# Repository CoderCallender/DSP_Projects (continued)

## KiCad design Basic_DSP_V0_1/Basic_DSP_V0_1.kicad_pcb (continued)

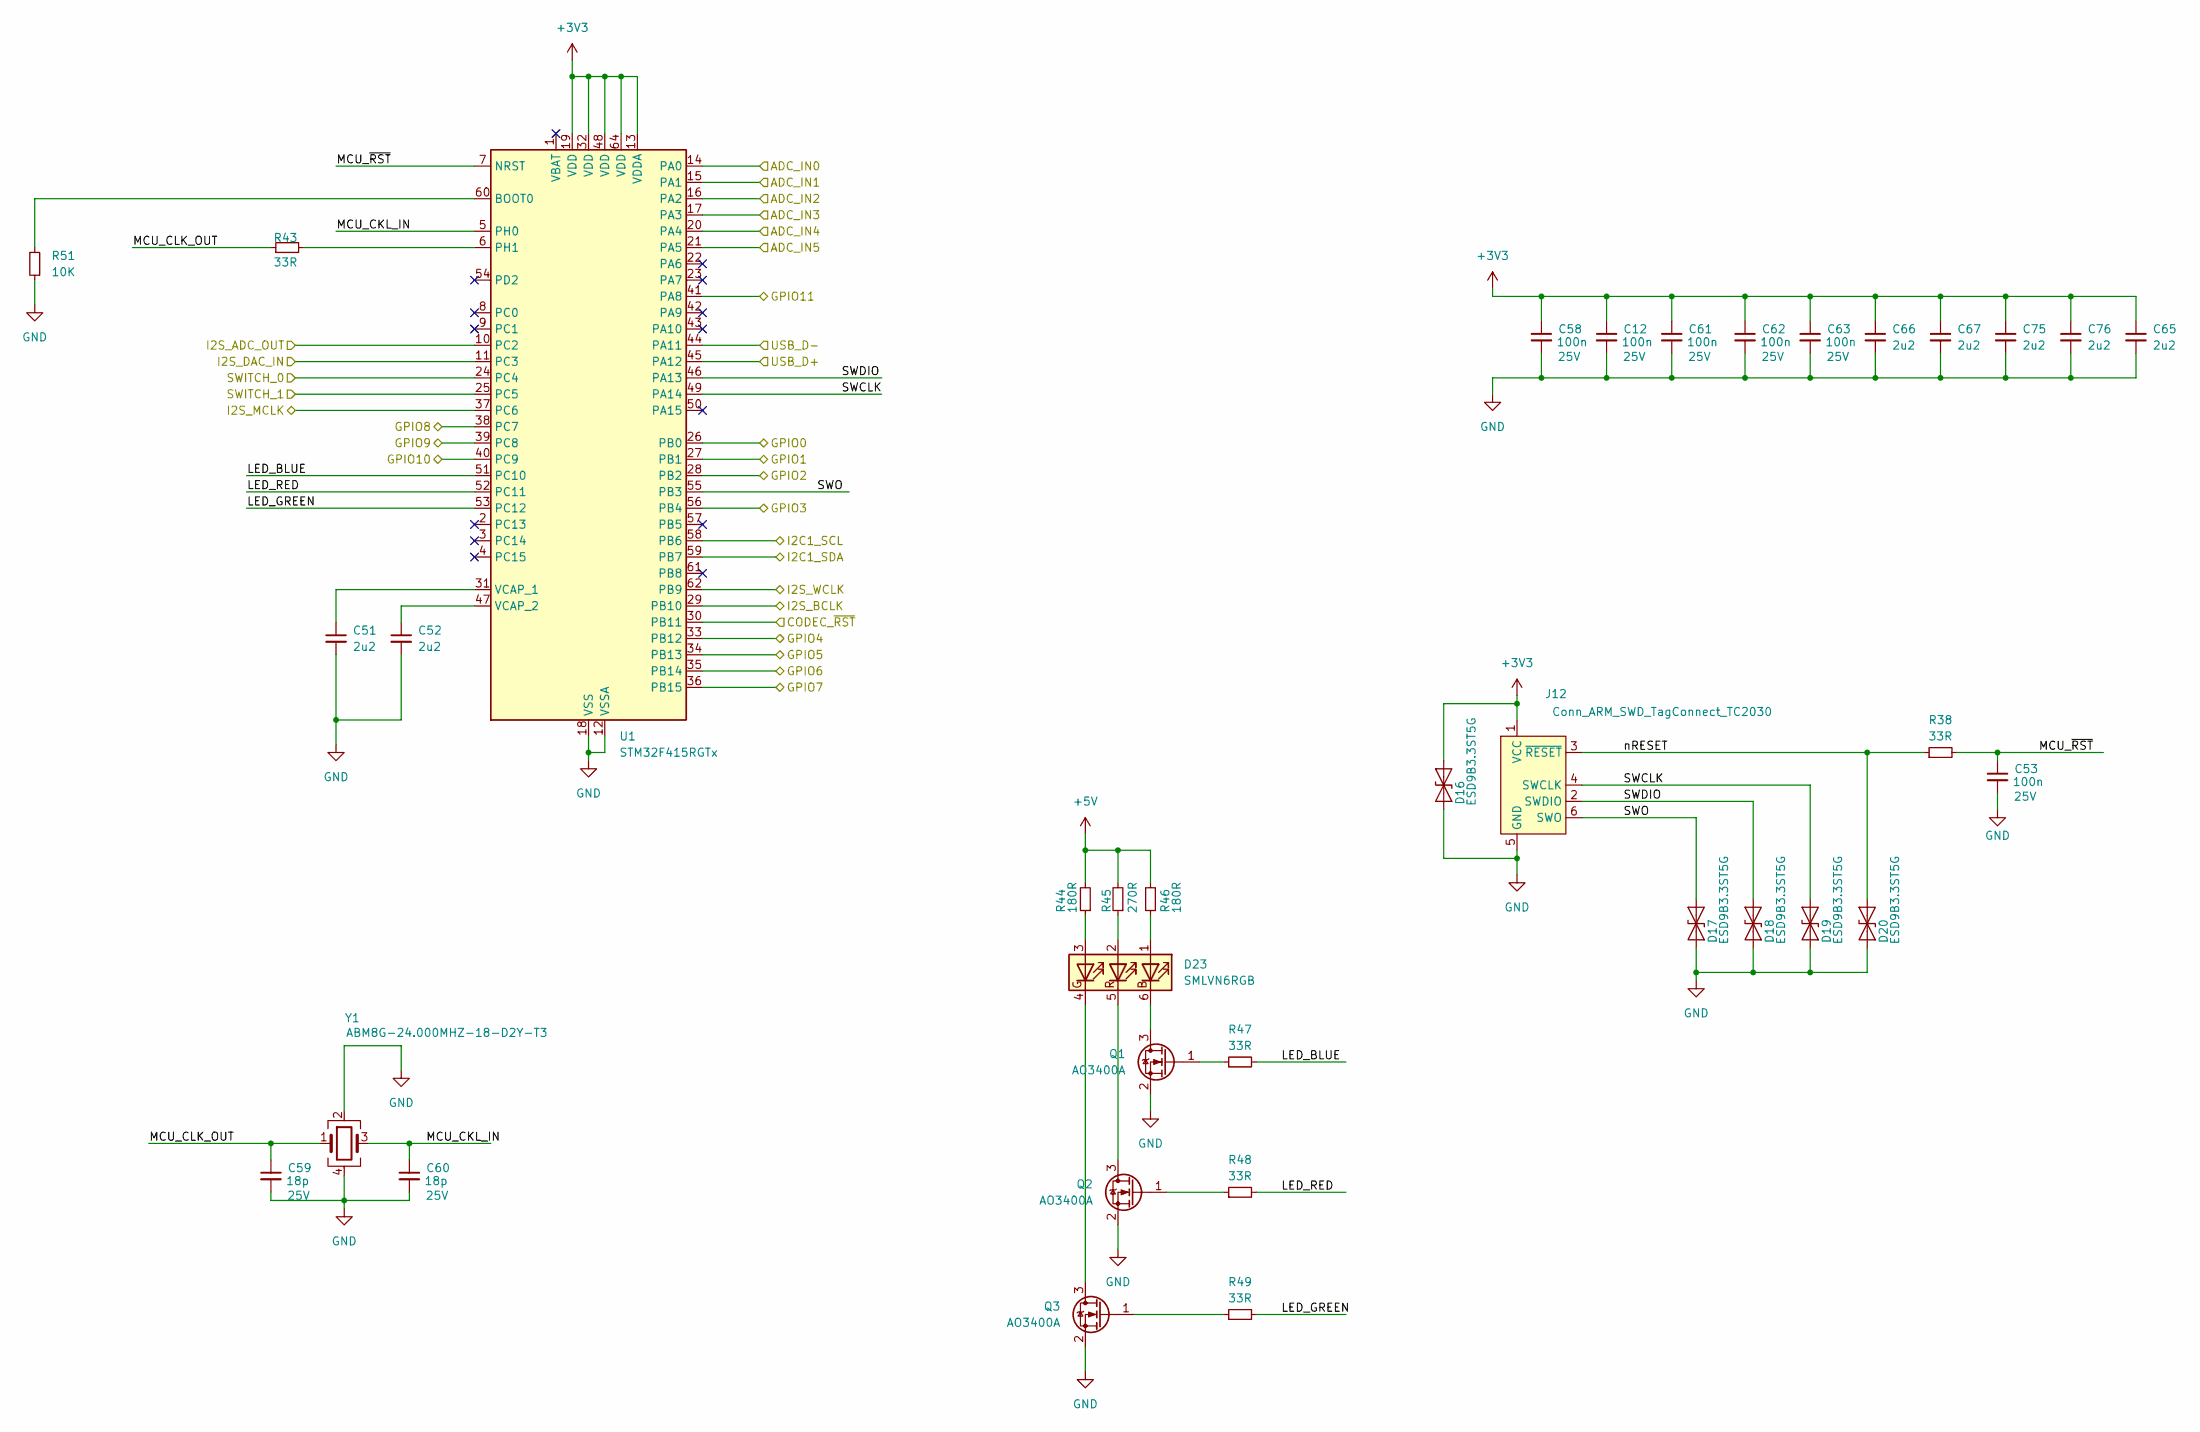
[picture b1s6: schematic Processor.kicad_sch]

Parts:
C12, C53, C58, C61, C62, C63: 100n; C_0603_1608Metric_Pad1.08x0.95mm_HandSolder; Voltage 25V; MPN 0603B104M250NT
C51, C52, C65, C66, C67, C75, C76: 2u2; C_0603_1608Metric_Pad1.08x0.95mm_HandSolder; Voltage 25V; MPN 0603B225K250NT
C59, C60: 18p; C_0603_1608Metric_Pad1.08x0.95mm_HandSolder; Voltage 25V; MPN RF18N180F500CT
D16, D17, D18, D19, D20: ESD9B3.3ST5G; D_SOD-923; MPN ESD9B3.3ST5G
D23: SMLVN6RGB; LED_ROHM_SMLVN6; MPN SMLVN6RGB1W1
J12: Conn_ARM_SWD_TagConnect_TC2030; Tag-Connect_TC2030-IDC-FP_2x03_P1.27mm_Vertical
Q1, Q2, Q3: AO3400A; SOT-23; MPN AO3400A
R38, R43, R47, R48, R49: 33R; R_0603_1608Metric_Pad0.98x0.95mm_HandSolder; MPN WR06X33R0FTL
R44, R46: 180R; R_0603_1608Metric_Pad0.98x0.95mm_HandSolder; MPN 0603WAF1800T5E
R45: 270R; R_0603_1608Metric_Pad0.98x0.95mm_HandSolder; MPN 0603WAF2700T5E
R51: 10K; R_0603_1608Metric_Pad0.98x0.95mm_HandSolder; MPN 0603WAF1002T5E
U1: STM32F415RGTx; LQFP-64_10x10mm_P0.5mm; MPN STM32F415RGT6
Y1: ABM8G-24.000MHZ-18-D2Y-T3; Crystal_SMD_Abracon_ABM8G-4Pin_3.2x2.5mm

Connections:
+3V3: C12.1, C58.1, C61.1, C62.1, C63.1, C65.1, C66.1, C67.1, C75.1, C76.1, D16.2 (A2), J12.1 (VCC), U1.13 (VDDA), U1.19 (VDD), U1.32 (VDD), U1.48 (VDD), U1.64 (VDD); also elsewhere on the board
+5V: R44.2, R45.2, R46.2; also elsewhere on the board
/CODEC/CODEC_~RST: U1.30 (PB11); also elsewhere on the board
/CODEC/I2C1_SCL: U1.58 (PB6); also elsewhere on the board
/CODEC/I2C1_SDA: U1.59 (PB7); also elsewhere on the board
/CODEC/I2S_ADC_OUT: U1.10 (PC2); also elsewhere on the board
/CODEC/I2S_BCLK: U1.29 (PB10); also elsewhere on the board
/CODEC/I2S_DAC_IN: U1.11 (PC3); also elsewhere on the board
/CODEC/I2S_MCLK: U1.37 (PC6); also elsewhere on the board
/CODEC/I2S_WCLK: U1.62 (PB9); also elsewhere on the board
/Connections/ADC_IN0: U1.14 (PA0); also elsewhere on the board
/Connections/ADC_IN1: U1.15 (PA1); also elsewhere on the board
/Connections/ADC_IN2: U1.16 (PA2); also elsewhere on the board
/Connections/ADC_IN3: U1.17 (PA3); also elsewhere on the board
/Connections/ADC_IN4: U1.20 (PA4); also elsewhere on the board
/Connections/ADC_IN5: U1.21 (PA5); also elsewhere on the board
/Connections/GPIO0: U1.26 (PB0); also elsewhere on the board
/Connections/GPIO1: U1.27 (PB1); also elsewhere on the board
/Connections/GPIO2: U1.28 (PB2); also elsewhere on the board
/Connections/GPIO3: U1.56 (PB4); also elsewhere on the board
/Connections/GPIO4: U1.33 (PB12); also elsewhere on the board
/Connections/GPIO5: U1.34 (PB13); also elsewhere on the board
/Connections/GPIO6: U1.35 (PB14); also elsewhere on the board
/Connections/GPIO7: U1.36 (PB15); also elsewhere on the board
/Connections/GPIO8: U1.38 (PC7); also elsewhere on the board
/Connections/GPIO9: U1.39 (PC8); also elsewhere on the board
/Connections/GPIO10: U1.40 (PC9); also elsewhere on the board
/Connections/GPIO11: U1.41 (PA8); also elsewhere on the board
/Connections/SWITCH_0: U1.24 (PC4); also elsewhere on the board
/Connections/SWITCH_1: U1.25 (PC5); also elsewhere on the board
/Connections/USB_D+: U1.45 (PA12); also elsewhere on the board
/Connections/USB_D-: U1.44 (PA11); also elsewhere on the board
/Processor/LED_BLUE: R47.2, U1.51 (PC10)
/Processor/LED_GREEN: R49.2, U1.53 (PC12)
/Processor/LED_RED: R48.2, U1.52 (PC11)
/Processor/MCU_CKL_IN: C60.1, U1.5 (PH0), Y1.3
/Processor/MCU_CLK_OUT: C59.1, R43.1, Y1.1
/Processor/MCU_~RST: C53.1, R38.2, U1.7 (NRST)
/Processor/SWCLK: D19.2 (A2), J12.4 (SWCLK), U1.49 (PA14)
/Processor/SWDIO: D18.2 (A2), J12.2 (SWDIO), U1.46 (PA13)
/Processor/SWO: D17.2 (A2), J12.6 (SWO), U1.55 (PB3)
/Processor/nRESET: D20.2 (A2), J12.3 (~RESET), R38.1
GND: C12.2, C51.2, C52.2, C53.2, C58.2, C59.2, C60.2, C61.2, C62.2, C63.2, C65.2, C66.2, C67.2, C75.2, C76.2, D16.1 (A1), D17.1 (A1), D18.1 (A1), D19.1 (A1), D20.1 (A1), J12.5 (GND), Q1.2 (S), Q2.2 (S), Q3.2 (S), R51.1, U1.12 (VSSA), U1.18 (VSS), U1.63 (VSS), Y1.2, Y1.4; also elsewhere on the board
unnamed: D23.1 (BA), R46.1
unnamed: D23.6 (BK), Q1.3 (D)
unnamed: D23.3 (GA), R44.1
unnamed: D23.4 (GK), Q3.3 (D)
unnamed: D23.2 (RA), R45.1
unnamed: D23.5 (RK), Q2.3 (D)
unnamed: Q1.1 (G), R47.1
unnamed: Q2.1 (G), R48.1
unnamed: Q3.1 (G), R49.1
unnamed: R51.2, U1.60 (BOOT0)
unnamed: R43.2, U1.6 (PH1)
unnamed: C51.1, U1.31 (VCAP_1)
unnamed: C52.1, U1.47 (VCAP_2)

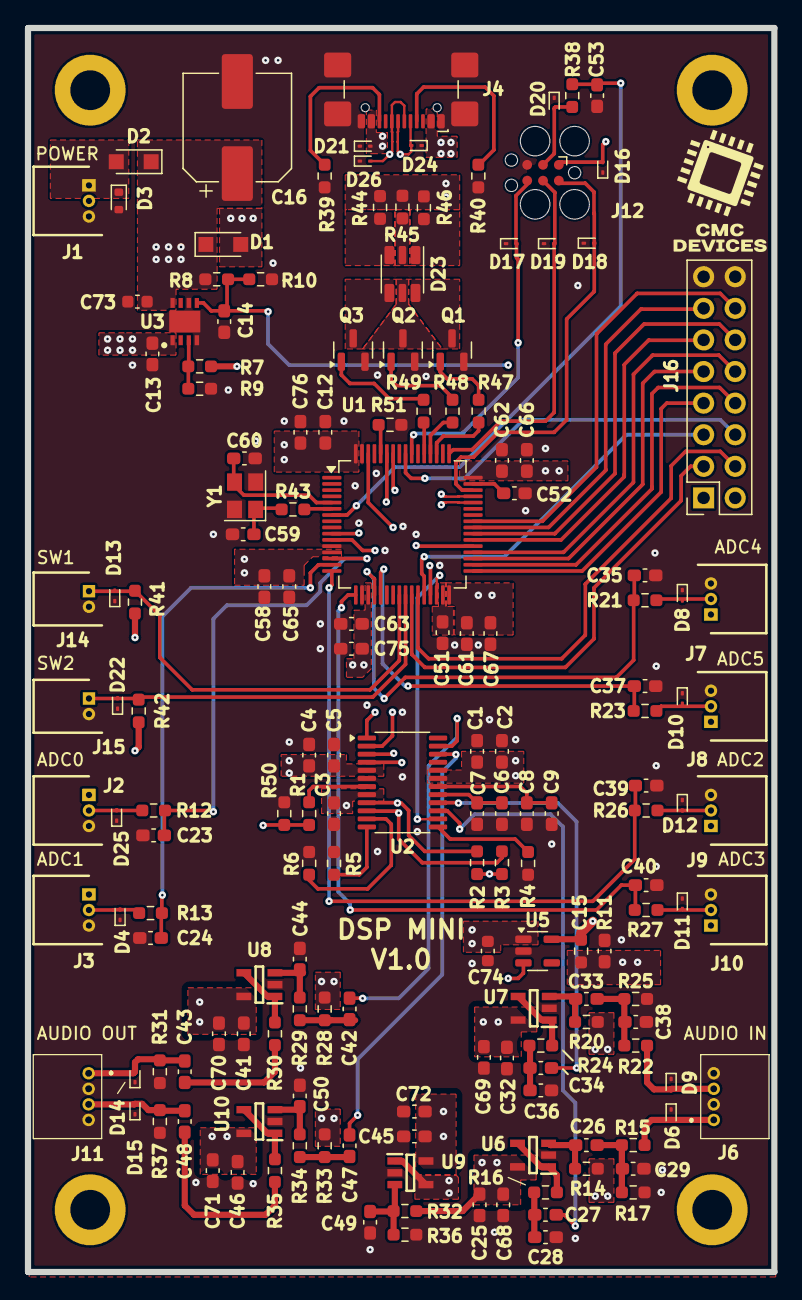
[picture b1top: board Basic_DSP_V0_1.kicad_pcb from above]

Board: 6 copper layers, 60.0 x 100.0 mm, 165 parts (0 on the bottom side), 102 nets.

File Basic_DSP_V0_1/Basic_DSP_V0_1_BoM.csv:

Comment,Designator,Footprint,JLCPCB Part #,Qty,DNP,MF,MPN,Manufacturer_Part_Number,Mouser Part Number,OC_MOUSER,Voltage
220uF,C16,Capacitor_SMD:CP_Elec_8x10.5,C5162357,1,,ROQANG ,CK1V221M-CRF10,,,,35V
100n,"C1,C3,C5,C6,C8,C12,C14,C23,C24,C25,C32,C35,C37,C39,C40,C41,C45,C46,C53,C58,C61,C62,C63",Capacitor_SMD:C_0603_1608Metric_Pad1.08x0.95mm_HandSolder,C336628,23,,FH (Guangdong Fenghua Advanced Tech) ,0603B104M250NT,,,963-BAST105SB7104KF,25V
22u,"C15,C49",Capacitor_SMD:C_0603_1608Metric_Pad1.08x0.95mm_HandSolder,C6119868,2,,HRE,CGA0603X5R226M160JT,,,187-CL32B226MOJNNNE,16V
2u2,"C2,C4,C13,C51,C52,C65,C66,C67,C68,C69,C70,C71,C72,C75,C76",Capacitor_SMD:C_0603_1608Metric_Pad1.08x0.95mm_HandSolder,C99228,15,,FH (Guangdong Fenghua Advanced Tech) ,0603B225K250NT,,,-- mixed values --,25V
10n,"C26,C33,C42,C47",Capacitor_SMD:C_0603_1608Metric_Pad1.08x0.95mm_HandSolder,C445734,4,,TDK ,CGA3E2X8R2A103KT0Y0H,,,,
220p,"C28,C29,C36,C38",Capacitor_SMD:C_0603_1608Metric_Pad1.08x0.95mm_HandSolder,C302062,4,,Walsin Tech Corp,0603N221J500CT,,,,
1n,"C44,C50",Capacitor_SMD:C_0603_1608Metric_Pad1.08x0.95mm_HandSolder,C161114,2,,Murata Electronics ,GCJ188R71H102KA01D,,,,
18p,"C59,C60",Capacitor_SMD:C_0603_1608Metric_Pad1.08x0.95mm_HandSolder,C2909435,2,,Walsin Tech Corp ,RF18N180F500CT,,,963-BAST105SB7104KF,25V
10u,"C7,C9,C27,C34,C43,C48",Capacitor_SMD:C_0603_1608Metric_Pad1.08x0.95mm_HandSolder,C96446,6,,Samsung Electro-Mechanics ,CL10A106MA8NRNC,,,-- mixed values --,-- mixed values --
10uF,"C73,C74",Capacitor_SMD:C_0603_1608Metric,C96446,2,,Samsung Electro-Mechanics ,CL10A106MA8NRNC,,,581-06033D106MAT2A,
ESD5Z12T1G/T5G,D3,Diode_SMD:D_SOD-523,C7436544,1,,FUXINSEMI,ESD5Z12T1G,,,,12V
SMLVN6RGB,D23,LED_SMD:LED_ROHM_SMLVN6,C2842809,1,,ROHM Semicon,SMLVN6RGB1W1,,,,
PMEG4030ER,"D1,D2",Diode_SMD:Nexperia_CFP3_SOD-123W,C5366303,2,,Shikues ,PMEG4030ER,,,,
ESD9B3.3ST5G,"D4,D8,D10,D11,D12,D13,D16,D17,D18,D19,D20,D22,D25",Diode_SMD:D_SOD-923,C3040608,13,,TECH PUBLIC ,ESD9B3.3ST5G,,,,
ESD9B5.0ST5G,"D6,D9,D14,D15,D21,D24,D26",Diode_SMD:D_SOD-923,C3021104,7,,TECH PUBLIC , ESD9B5.0ST5G,,,,
USB_C_Receptacle_USB2.0_16P,J4,Connector_USB:USB_C_Receptacle_GCT_USB4110,,1,,,,,,,
Conn_02x08_Odd_Even,J16,Connector_PinSocket_2.54mm:PinSocket_2x08_P2.54mm_Vertical,,1,,DNP,,,,,
53048-0310,"J1,J2,J3,J7,J8,J9,J10",Chase_Conn:SHDRRA3W35P0X125_1X3_550X550X350P,C505275,7,, MOLEX ,530480310,53048-0310,538-53048-0310,,
53048-0210,"J14,J15",Chase_Conn:SHDRRA2W35P0X125_1X2_425X550X350P,C505099,2,,MOLEX,530480210,53048-0210,538-53048-0210,,
53048-0410,"J6,J11",Chase_Conn:530480410,C588275,2,,MOLEX,530480410,53048-0410,538-53048-0410,,
AO3400A,"Q1,Q2,Q3",Package_TO_SOT_SMD:SOT-23,C20917,3,,Alpha & Omega Semicon ,AO3400A,,,,
0R,R7,Resistor_SMD:R_0603_1608Metric_Pad0.98x0.95mm_HandSolder,C21189,1,,UNI-ROYAL(Uniroyal Elec) ,0603WAF0000T5E,,,,
0R,R11,Resistor_SMD:R_0603_1608Metric_Pad0.98x0.95mm_HandSolder,C22859,1,,UNI-ROYAL(Uniroyal Elec) ,0603WAF100JT5E,,,,
270R,R45,Resistor_SMD:R_0603_1608Metric_Pad0.98x0.95mm_HandSolder,C22966,1,,UNI-ROYAL(Uniroyal Elec),0603WAF2700T5E,,,,
47K,R50,Resistor_SMD:R_0603_1608Metric_Pad0.98x0.95mm_HandSolder,C105579,1,,YAGEO ,RC0603FR-0747KL,,,,
33R,"R1,R12,R13,R21,R23,R26,R27,R38,R43,R47,R48,R49",Resistor_SMD:R_0603_1608Metric_Pad0.98x0.95mm_HandSolder,C163909,12,,Walsin Tech Corp ,WR06X33R0FTL,,,,
1M,"R14,R17,R20,R25,R28,R33",Resistor_SMD:R_0603_1608Metric_Pad0.98x0.95mm_HandSolder,C22935,6,,UNI-ROYAL(Uniroyal Elec) ,0603WAF1004T5E,,,,
100R,"R15,R22,R30,R35",Resistor_SMD:R_0603_1608Metric_Pad0.98x0.95mm_HandSolder,C105588,4,, YAGEO , RC0603FR-07100RL,,,,
1K,"R16,R24,R29,R34",Resistor_SMD:R_0603_1608Metric_Pad0.98x0.95mm_HandSolder,C25585,4,,UNI-ROYAL(Uniroyal Elec),0603WAJ0102T5E,,,,
2k2,"R2,R3",Resistor_SMD:R_0603_1608Metric_Pad0.98x0.95mm_HandSolder,C4190,2,,UNI-ROYAL(Uniroyal Elec) ,0603WAF2201T5E,,,,
5k1,"R39,R40",Resistor_SMD:R_0603_1608Metric_Pad0.98x0.95mm_HandSolder,C23186,2,,UNI-ROYAL(Uniroyal Elec),0603WAF5101T5E,,,,
10K,"R4,R5,R6,R31,R37,R51",Resistor_SMD:R_0603_1608Metric_Pad0.98x0.95mm_HandSolder,C25804,6,,UNI-ROYAL(Uniroyal Elec) ,0603WAF1002T5E,,,,
100K,"R41,R42",Resistor_SMD:R_0603_1608Metric_Pad0.98x0.95mm_HandSolder,C14675,2,,YAGEO ,RC0603FR-07100KL,,,,
180R,"R44,R46",Resistor_SMD:R_0603_1608Metric_Pad0.98x0.95mm_HandSolder,C22828,2,,UNI-ROYAL(Uniroyal Elec) ,0603WAF1800T5E,,,,
47k,"R8,R9,R10,R32,R36",Resistor_SMD:R_0603_1608Metric_Pad0.98x0.95mm_HandSolder,C105579,5,,YAGEO ,  RC0603FR-0747KL,,,,
STM32F415RGTx,U1,Package_QFP:LQFP-64_10x10mm_P0.5mm,C124726,1,,STMicroelectronics,STM32F415RGT6,,,,
CS4270,U2,Package_SO:TSSOP-24_4.4x7.8mm_P0.65mm,C1323229,1,,Cirrus Logic,CS4270-CZZR,,,,
TLV76733QWDRBRQ1,U3,Chase_LDO:SON65P300X300X100-9N-D,C5220143,1,,Texas Instruments,TLV76733QWDRBRQ1,TLV76733QWDRBRQ1,595-TLV76733QWDRBRQ1,,
NCP718BSN500T1G,U5,Package_TO_SOT_SMD:SOT-23-5,C892796,1,,onsemi , NCP718BSN500T1G,,,,
TLV9161IDBVR,"U6,U7,U8,U9,U10",Chase_OPAMP:SOT95P280X145-5N,C4368955,5,,Texas Instruments ,TLV9161IDBVR,TLV9161IDBVR,595-TLV9161IDBVR,,
ABM8G-24.000MHZ-18-D2Y-T3,Y1,Crystal:Crystal_SMD_Abracon_ABM8G-4Pin_3.2x2.5mm,,1,,,,,,,

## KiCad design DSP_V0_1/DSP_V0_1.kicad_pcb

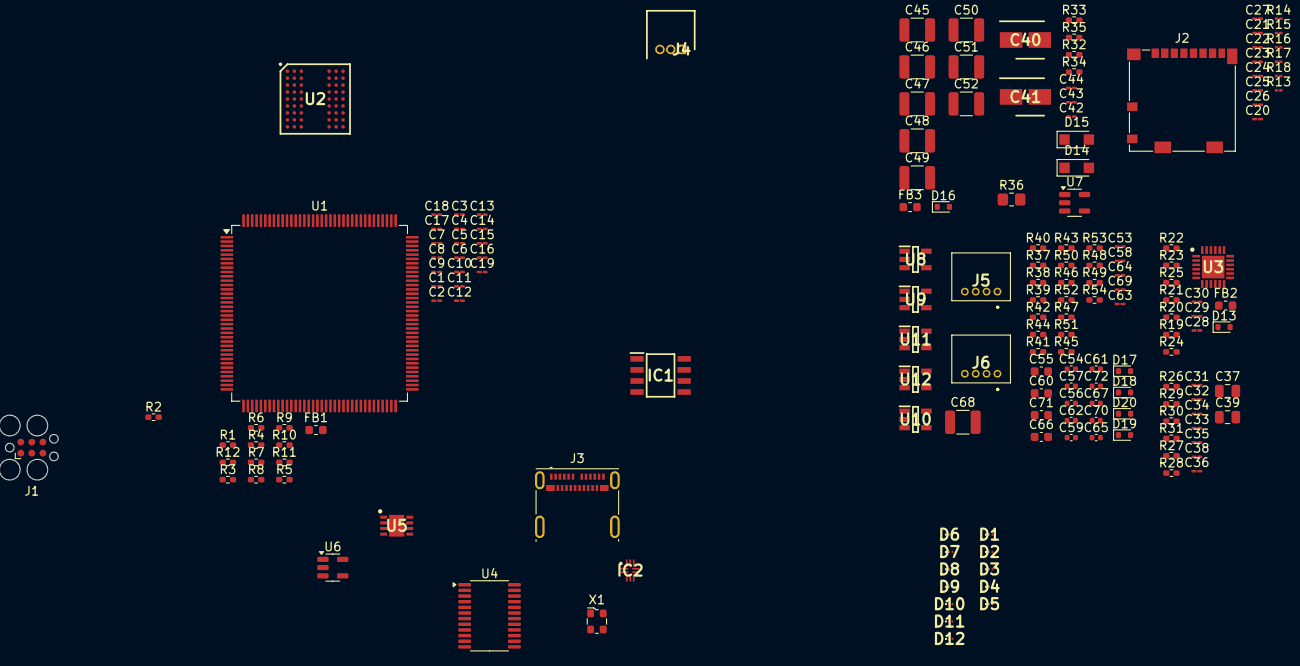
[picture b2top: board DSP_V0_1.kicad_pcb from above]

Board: 2 copper layers, 170 parts (0 on the bottom side), 132 nets, no tracks yet.

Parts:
C1, C2, C3, C4, C5, C6, C7, C8, C9, C10, C11, C12, C13, C14, C15, C16, C19, C21, C22, C23, C24, C25, C26, C27, C28, C29, C31, C33, C35, C36, C38, C44, C53, C58, C63, C64, C69: 100n; C_01005_0402Metric_Pad0.57x0.30mm_HandSolder
C17, C18, C20, C30, C32, C34, C42, C43: 2u2; C_01005_0402Metric_Pad0.57x0.30mm_HandSolder
C37, C39: 10u; C_0805_2012Metric
C40, C41: 2u2; CAPAE430X550N
C45, C46, C47, C48, C49, C50, C51, C52, C68: 22u; C_1210_3225Metric
C54, C59, C65, C70: 10n; C_0402_1005Metric
C55, C60, C66, C71: 10u; C_0603_1608Metric
C56, C57, C61, C62: 220p; C_0402_1005Metric
C67, C72: 1n; C_0402_1005Metric
D1, D2, D3, D4, D5, D6, D7, D8, D9, D10, D11, D12: PESD3V3Z1BSFYL; PMEG3005AESFYL
D13, D17, D18, D19, D20: ESD5Z5.0T1G/T5G; D_SOD-523
D14, D15: PMEG4030ER; Nexperia_CFP3_SOD-123W
D16: ESD5Z12T1G/T5G; D_SOD-523
FB1, FB2, FB3: 120R; L_0603_1608Metric
IC1: IS25LP080D-JNLE-TR; SOIC127P600X175-8N
IC2: NX3DV42GU,115; QFN40P140X180X50-10N
J1: Conn_ARM_SWD_TagConnect_TC2030; Tag-Connect_TC2030-IDC-FP_2x03_P1.27mm_Vertical
J2: Micro_SD_Card_Det2; microSD_HC_Molex_104031-0811
J3: USB_C_Receptacle; USB_C_Receptacle_Molex_105450-0101
J4: 53048-0310; SHDRRA3W35P0X125_1X3_550X550X350P
J5, J6: 53048-0410; 530480410
R1, R22, R23, R24, R25: 5k1; R_0402_1005Metric_Pad0.72x0.64mm_HandSolder
R2, R32: 0R; R_0402_1005Metric_Pad0.72x0.64mm_HandSolder
R3, R4, R5, R6, R7, R8, R9, R10, R11, R12, R19, R26: 33R; R_0402_1005Metric_Pad0.72x0.64mm_HandSolder
R13, R14, R15, R16, R17, R18: 47k; R_01005_0402Metric
R20: 8k06; R_0402_1005Metric_Pad0.72x0.64mm_HandSolder
R21, R33, R34, R35, R46, R50: 47k; R_0402_1005Metric_Pad0.72x0.64mm_HandSolder
R27, R28: 2k2; R_0402_1005Metric_Pad0.72x0.64mm_HandSolder
R29, R30, R31, R49, R54: 10K; R_0402_1005Metric_Pad0.72x0.64mm_HandSolder
R36: 10R; R_0805_2012Metric_Pad1.20x1.40mm_HandSolder
R37, R40, R41, R44, R45, R51: 1M; R_0402_1005Metric_Pad0.72x0.64mm_HandSolder
R38, R42, R48, R53: 100R; R_0402_1005Metric_Pad0.72x0.64mm_HandSolder
R39, R43, R47, R52: 1K; R_0402_1005Metric_Pad0.72x0.64mm_HandSolder
U1: STM32H723ZGT6; LQFP-144_20x20mm_P0.5mm
U2: IS42S16800F-6BL; BGA54C80P9X9_800X800X120
U3: USB3318C-CP-TR; QFN50P400X400X100-25N-D
U4: CS4270; TSSOP-24_4.4x7.8mm_P0.65mm
U5: TLV76733QWDRBRQ1; SON65P300X300X100-9N-D
U6: NCP718ASN180T1G; SOT-23-5
U7: NCP718BSN500T1G; SOT-23-5
U8, U9, U10, U11, U12: TLV9161IDBVR; SOT95P280X145-5N
X1: ECS-2520MV-130-BN-TR; Oscillator_SMD_ECS_2520MV-xxx-xx-4Pin_2.5x2.0mm

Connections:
+1V8: C42.1, U3.21 (VDD1.8), U6.5 (OUT)
+3V3: C1.1, C2.1, C3.1, C4.1, C5.1, C6.1, C7.1, C10.1, C11.1, C12.1, C13.1, C14.1, C15.1, C16.1, C20.1, C21.1, C22.1, C23.1, C24.1, C25.1, C26.1, C27.1, C33.1, C34.1, C35.1, C43.1, D1.1 (K1), FB1.1, IC1.8 (VCC), IC2.9 (VCC), J1.1 (VCC), J2.4 (VDD), R2.1, R13.1, R14.1, R15.1, R16.1, R17.1, R18.1, R21.2, R27.2, R28.2, R32.1, U1.6 (VBAT), U1.17 (VDD), U1.30 (VDD), U1.39 (VDD), U1.52 (VDD), U1.62 (VDD), U1.72 (VDD), U1.84 (VDD), U1.95 (VDD33USB), U1.108 (VDD), U1.121 (VDD), U1.131 (VDD), U1.144 (VDD), U2.A7 (VDDQ_1), U2.A9 (VDD_1), U2.B3 (VDDQ_2), U2.C7 (VDDQ_3), U2.D3 (VDDQ_4), U2.E7 (VDD_2), U2.J9 (VDD_3), U3.4 (VDD3.3), U3.17 (VDDIO), U4.5 (VD), U4.8 (VLC), U5.1 (OUT), U6.1 (IN), X1.1 (Tri-State), X1.4 (VDD)
+3V3_FILT: C8.1, C9.1, FB1.2, U1.32 (VREF+), U1.33 (VDDA)
+5V: R36.1, U7.5 (OUT)
+5VA: C31.1, C32.1, C45.1, C46.1, C47.1, C48.1, C49.1, C50.1, C51.1, C52.1, C53.1, C58.1, C63.1, C64.1, C69.1, R36.2, R46.1, U4.19 (VA), U8.5 (V+), U9.5 (V+), U10.5 (V+), U11.5 (V+), U12.5 (V+)
+VREF: R37.1, R41.1, R45.1, R51.1, U11.1 (OUT), U11.4 (IN-)
/Analog/AUDIO_IN_L: D17.1 (K), J5.1, R38.1
/Analog/AUDIO_IN_R: D18.1 (K), J5.3, R42.1
/Analog/AUDIO_OUT_L: C66.2, D19.1 (K), J6.1, R49.2
/Analog/AUDIO_OUT_R: C71.2, D20.1 (K), J6.3, R54.2
/CODEC Sheet/CODEC_OUT: R26.1, U4.7 (SDOUT)
/CODEC Sheet/CODEC_~RST: U1.7 (PC13), U4.14 (~RST)
/CODEC Sheet/I2C4_SCL: R28.1, U1.81 (PD12), U4.10 (SCL/CCLK/M0)
/CODEC Sheet/I2C4_SDA: R27.1, U1.82 (PD13), U4.9 (SDA/CDOUT/M1)
/CODEC Sheet/I2S_ADC_OUT: R26.2, U1.2 (PE3)
/CODEC Sheet/I2S_BCLK: R10.1, U4.4 (SCLK)
/CODEC Sheet/I2S_DAC_IN: R11.1, U4.1 (SDIN)
/CODEC Sheet/I2S_MCLK: R8.1, U4.3 (MCLK)
/CODEC Sheet/I2S_WCLK: R9.1, U4.2 (LRCLK)
/Memory/QSPI_IO0: IC1.5 (SI(IO0)), U1.20 (PF8)
/Memory/QSPI_IO1: IC1.2 (SO(IO1)), U1.21 (PF9)
/Memory/QSPI_IO2: IC1.3 (WP#(IO2)), U1.19 (PF7)
/Memory/QSPI_IO3: IC1.7 (HOLD#_OR_RESET#_(IO3)), U1.18 (PF6)
/Memory/QSPI_SCK: IC1.6 (SCK), R7.1
/Memory/QSPI_~CE: IC1.1 (CE#), U1.91 (PG6)
/Memory/RAM_A0: U1.10 (PF0), U2.H7 (A0)
/Memory/RAM_A1: U1.11 (PF1), U2.H8 (A1)
/Memory/RAM_A2: U1.12 (PF2), U2.J8 (A2)
/Memory/RAM_A3: U1.13 (PF3), U2.J7 (A3)
/Memory/RAM_A4: U1.14 (PF4), U2.J3 (A4)
/Memory/RAM_A5: U1.15 (PF5), U2.J2 (A5)
/Memory/RAM_A6: U1.50 (PF12), U2.H3 (A6)
/Memory/RAM_A7: U1.53 (PF13), U2.H2 (A7)
/Memory/RAM_A8: U1.54 (PF14), U2.H1 (A8)
/Memory/RAM_A9: U1.55 (PF15), U2.G3 (A9)
/Memory/RAM_A10: U1.56 (PG0), U2.H9 (A10)
/Memory/RAM_A11: U1.57 (PG1), U2.G2 (A11)
/Memory/RAM_BA0: U1.89 (PG4), U2.G7 (BA0)
/Memory/RAM_BA1: U1.90 (PG5), U2.G8 (BA1)
/Memory/RAM_CKE: U1.45 (PC5), U2.F3 (CKE)
/Memory/RAM_CLK: R5.1, U2.F2 (CLK)
/Memory/RAM_D0: U1.85 (PD14), U2.A8 (DQ0)
/Memory/RAM_D1: U1.86 (PD15), U2.B9 (DQ1)
/Memory/RAM_D2: U1.114 (PD0), U2.B8 (DQ2)
/Memory/RAM_D3: U1.115 (PD1), U2.C9 (DQ3)
/Memory/RAM_D4: U1.58 (PE7), U2.C8 (DQ4)
/Memory/RAM_D5: U1.59 (PE8), U2.D9 (DQ5)
/Memory/RAM_D6: U1.60 (PE9), U2.D8 (DQ6)
/Memory/RAM_D7: U1.63 (PE10), U2.E9 (DQ7)
/Memory/RAM_D8: U1.64 (PE11), U2.E1 (DQ8)
/Memory/RAM_D9: U1.65 (PE12), U2.D2 (DQ9)
/Memory/RAM_D10: U1.66 (PE13), U2.D1 (DQ10)
/Memory/RAM_D11: U1.67 (PE14), U2.C2 (DQ11)
/Memory/RAM_D12: U1.68 (PE15), U2.C1 (DQ12)
/Memory/RAM_D13: U1.77 (PD8), U2.B2 (DQ13)
/Memory/RAM_D14: U1.78 (PD9), U2.B1 (DQ14)
/Memory/RAM_D15: U1.79 (PD10), U2.A2 (DQ15)
/Memory/RAM_DQMH: U1.142 (PE1), U2.F1 (DQMH)
/Memory/RAM_DQML: U1.141 (PE0), U2.E8 (DQML)
/Memory/RAM_NCAS: U1.132 (PG15), U2.F7 (~CAS)
/Memory/RAM_NCS: U1.44 (PC4), U2.G9 (~CS)
/Memory/RAM_NRAS: U1.49 (PF11), U2.F8 (~RAS)
/Memory/RAM_NWE: U1.43 (PA7), U2.F9 (~WE)
/Memory/SD_CLK: D11.2 (K2), J2.5 (CLK), U1.122 (PD6)
/Memory/SD_CMD: D7.2 (K2), J2.3 (CMD), R15.2, U1.123 (PD7)
/Memory/SD_D0: D8.2 (K2), J2.7 (DAT0), R16.2, U1.124 (PG9)
/Memory/SD_D1: D9.2 (K2), J2.8 (DAT1), R17.2, U1.125 (PG10)
/Memory/SD_D2: D12.2 (K2), J2.1 (DAT2), R13.2, U1.126 (PG11)
/Memory/SD_D3: D6.2 (K2), J2.2 (DAT3/CD), R14.2, U1.127 (PG12)
/Memory/SD_DET: D10.2 (K2), J2.10 (DET_A), R18.2, U1.128 (PG13)
/Power/V_ENABLE: C44.1, R33.2, R35.1, U5.5 (EN), U6.3 (EN), U7.3 (EN)
/Processor/MCU_SWCLK: R4.1, U1.109 (PA14(JTCK)
/Processor/MCU_SWDIO: R3.1, U1.105 (PA13(JTMS)
/Processor/MCU_SWO: R6.1, U1.133 (PB3(JTDO)
/Processor/MCU_~RST: C19.1, R12.2, U1.25 (NRST)
/Processor/SWCLK: D4.1 (K1), J1.4 (SWCLK), R4.2
/Processor/SWDIO: D3.1 (K1), J1.2 (SWDIO), R3.2
/Processor/SWO: D2.1 (K1), J1.6 (SWO), R6.2
/Processor/nRESET: D5.1 (K1), J1.3 (~RESET), R12.1
/USB/D+: IC2.1 (D+), J3.A6 (D+), J3.B6 (D+)
/USB/D-: IC2.2 (D-), J3.A7 (D-), J3.B7 (D-)
/USB/USB_HS_D+: IC2.5 (HSD1+), U3.6 (DP)
/USB/USB_HS_D-: IC2.4 (HSD1-), U3.5 (DM)
/USB/USB_SW: IC2.10 (S), R25.2
GND: C1.2, C2.2, C3.2, C4.2, C5.2, C6.2, C7.2, C8.2, C9.2, C10.2, C11.2, C12.2, C13.2, C14.2, C15.2, C16.2, C17.2, C18.2, C19.2, C20.2, C21.2, C22.2, C23.2, C24.2, C25.2, C26.2, C27.2, C28.2, C29.2, C30.2, C31.2, C32.2, C33.2, C34.2, C35.2, C36.2, C37.2, C38.2, C39.2, C40.2, C41.2, C42.2, C43.2, C44.2, C45.2, C46.2, C47.2, C48.2, C49.2, C50.2, C51.2, C52.2, C53.2, C56.1, C57.2, C58.2, C61.1, C62.2, C63.2, C64.2, C67.2, C68.2, C69.2, C72.2, D1.2 (K2), D2.2 (K2), D3.2 (K2), D4.2 (K2), D5.2 (K2), D6.1 (K1), D7.1 (K1), D8.1 (K1), D9.1 (K1), D10.1 (K1), D11.1 (K1), D12.1 (K1), D13.2 (A), D16.2 (A), D17.2 (A), D18.2 (A), D19.2 (A), D20.2 (A), IC1.4 (GND), IC2.8 (~OE), J1.5 (GND), J2.6 (VSS), J2.11 (SHIELD), J3.A1 (GND), J3.A12 (GND), J3.B1 (GND), J3.B12 (GND), J4.3, J5.2, J5.4, J6.2, J6.4, R1.1, R20.1, R22.1, R23.1, R25.1, R29.1, R30.1, R31.1, R34.2, R35.2, R40.2, R44.2, R49.1, R50.2, R54.1, U2.A1 (VSS_1), U2.A3 (VSSQ_1), U2.B7 (VSSQ_2), U2.C3 (VSSQ_3), U2.D7 (VSSQ_4), U2.E3 (VSS_2), U2.J1 (VSS_3), U4.6 (DGND), U4.20 (AGND), U5.4 (GND_1), U5.6 (GND_2), U5.9 (EP), U6.2 (GND), U7.2 (GND), U8.2 (V-), U9.2 (V-), U10.2 (V-), U11.2 (V-), U12.2 (V-), X1.2 (GND)
unnamed: C17.1, U1.71 (VCAP)
unnamed: C18.1, U1.106 (VCAP)
unnamed: C29.1, FB2.2
unnamed: C54.1, C57.1, R38.2, R40.1
unnamed: C55.1, C56.2, R39.2
unnamed: C59.1, C62.1, R42.2, R44.1
unnamed: C60.1, C61.2, R43.2
unnamed: C65.2, R45.2, R47.1
unnamed: C66.1, R48.2
unnamed: C70.2, R51.2, R52.1
unnamed: C71.1, R53.2
unnamed: C41.1, D14.1 (K), FB3.2, R33.1, U5.8 (IN), U7.1 (IN)
unnamed: C40.1, D15.1 (K), FB3.1
unnamed: J3.A5 (CC1), R23.2
unnamed: J3.B5 (CC2), R22.2
unnamed: R1.2, U1.138 (BOOT0)
unnamed: R2.2, U1.143 (PDR_ON)
unnamed: R8.2, U1.1 (PE2)
unnamed: R9.2, U1.3 (PE4)
unnamed: R10.2, U1.4 (PE5)
unnamed: R11.2, U1.5 (PE6)
unnamed: R7.2, U1.22 (PF10)
unnamed: R5.2, U1.93 (PG8)
unnamed: U1.16 (VSS), U1.38 (VSS), U1.51 (VSS), U1.61 (VSS), U1.83 (VSS), U1.94 (VSS), U1.107 (VSS), U1.120 (VSS), U1.130 (VSS)
unnamed: R20.2, U3.24 (RBIAS)
unnamed: R19.1, U3.23 (REFCLK)
unnamed: R21.1, U3.22 (RESETB)
unnamed: R24.1, U3.2 (VBUS)
unnamed: R31.2, U4.11 (AD0/~CS/I2S/~LJ)
unnamed: R30.2, U4.12 (AD1/CDIN/MDIV1)
unnamed: R29.2, U4.13 (AD2/MDIV2)
unnamed: C38.1, C39.1, U4.18 (FIL+)
unnamed: C36.1, C37.1, U4.17 (VQ)
unnamed: R32.2, R34.1, U5.3 (SNS)
unnamed: C54.2, R37.2, U8.3 (IN+)
unnamed: R39.1, U8.1 (OUT), U8.4 (IN-)
unnamed: C59.2, R41.2, U9.3 (IN+)
unnamed: R43.1, U9.1 (OUT), U9.4 (IN-)
unnamed: C67.1, R47.2, U10.3 (IN+)
unnamed: R48.1, U10.1 (OUT), U10.4 (IN-)
unnamed: C68.1, R46.2, R50.1, U11.3 (IN+)
unnamed: C72.1, R52.2, U12.3 (IN+)
unnamed: R53.1, U12.1 (OUT), U12.4 (IN-)
unnamed: R19.2, X1.3 (OUT)
VBUS: C28.1, D13.1 (K), FB2.1, J3.A4 (VBUS), J3.A9 (VBUS), J3.B4 (VBUS), J3.B9 (VBUS)
VBUS_FILT: C30.1, D14.2 (A), R24.2
VCC: D15.2 (A), D16.1 (K), J4.1

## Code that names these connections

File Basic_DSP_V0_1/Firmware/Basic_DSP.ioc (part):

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Mcu.Name=STM32F405RGTx
Mcu.Package=LQFP64
Mcu.UserName=STM32F405RGTx
PA0-WKUP.Signal=ADCx_IN0
PA1.Signal=ADCx_IN1
PA11.Mode=Device_Only
PA11.Signal=USB_OTG_FS_DM
PA12.Mode=Device_Only
PA12.Signal=USB_OTG_FS_DP
PA13.Mode=Trace_Asynchronous_SW
PA13.Signal=SYS_JTMS-SWDIO
PA14.Mode=Trace_Asynchronous_SW
PA14.Signal=SYS_JTCK-SWCLK
PA2.Signal=ADCx_IN2
PA3.Signal=ADCx_IN3
PA4.Signal=ADCx_IN4
PA5.Signal=ADCx_IN5
PA6.Signal=ADCx_IN6
PA7.Signal=ADCx_IN7
PA8.Signal=GPIO_Input
PB0.Signal=GPIO_Input
PB1.Signal=GPIO_Input
PB10.GPIOParameters=GPIO_Label
PB10.GPIO_Label=I2S_BCLK
PB10.Mode=Full_Duplex_Master
PB10.Signal=I2S2_CK
PB11.GPIOParameters=GPIO_Label
PB11.GPIO_Label=CODEC_RST
PB11.Signal=GPIO_Output
PB12.Signal=GPIO_Input
PB13.Signal=GPIO_Input
PB14.Signal=GPIO_Input
PB15.Signal=GPIO_Input
PB2.Signal=GPIO_Input
PB3.Mode=Trace_Asynchronous_SW
PB3.Signal=SYS_JTDO-SWO
PB6.Mode=I2C
PB6.Signal=I2C1_SCL
PB7.Mode=I2C
PB7.Signal=I2C1_SDA
PB9.Mode=Full_Duplex_Master
PB9.Signal=I2S2_WS
PC10.Signal=GPIO_Output
PC11.Signal=GPIO_Output
PC12.Signal=GPIO_Output
PC2.Mode=Full_Duplex_Master
PC2.Signal=I2S2_ext_SD
PC3.GPIOParameters=GPIO_Label
PC3.GPIO_Label=I2S_SDIN
PC3.Mode=Full_Duplex_Master
PC3.Signal=I2S2_SD
PC4.GPIOParameters=GPIO_Label
PC4.GPIO_Label=SWITCH_0
PC4.Signal=GPIO_Input
PC5.GPIOParameters=GPIO_Label
PC5.GPIO_Label=SWITCH_1
PC5.Signal=GPIO_Input
PC6.Mode=Master_Clock_Activated
PC6.Signal=I2S2_MCK
PC7.Signal=GPIO_Input
PC8.Signal=GPIO_Input
PC9.Signal=GPIO_Input
PH0-OSC_IN.Mode=HSE-External-Oscillator
PH0-OSC_IN.Signal=RCC_OSC_IN
PH1-OSC_OUT.Mode=HSE-External-Oscillator
PH1-OSC_OUT.Signal=RCC_OSC_OUT
RCC.HSE_VALUE=24000000
RCC.SYSCLKFreq_VALUE=24000000
RCC.SYSCLKSource=RCC_SYSCLKSOURCE_HSE
board=custom

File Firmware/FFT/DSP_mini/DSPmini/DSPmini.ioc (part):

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Mcu.Name=STM32F415RGTx
Mcu.Package=LQFP64
Mcu.UserName=STM32F415RGTx
PA0-WKUP.Signal=ADCx_IN0
PA1.Signal=ADCx_IN1
PA13.Mode=Serial_Wire
PA13.Signal=SYS_JTMS-SWDIO
PA14.Mode=Serial_Wire
PA14.Signal=SYS_JTCK-SWCLK
PA2.Signal=ADCx_IN2
PA3.Signal=ADCx_IN3
PA4.Signal=ADCx_IN4
PA5.Signal=ADCx_IN5
PB11.GPIOParameters=GPIO_Label
PB11.GPIO_Label=CODEC_RST
PB11.Signal=GPIO_Output
PB13.Mode=Full_Duplex_Master
PB13.Signal=I2S2_CK
PB6.Mode=I2C
PB6.Signal=I2C1_SCL
PB7.Mode=I2C
PB7.Signal=I2C1_SDA
PB9.Mode=Full_Duplex_Master
PB9.Signal=I2S2_WS
PC10.GPIOParameters=GPIO_Label
PC10.GPIO_Label=LED_BLUE
PC10.Signal=GPIO_Output
PC11.GPIOParameters=GPIO_Label
PC11.GPIO_Label=LED_RED
PC11.Signal=GPIO_Output
PC12.GPIOParameters=GPIO_Label
PC12.GPIO_Label=LED_GREEN
PC12.Signal=GPIO_Output
PC2.Mode=Full_Duplex_Master
PC2.Signal=I2S2_ext_SD
PC3.Mode=Full_Duplex_Master
PC3.Signal=I2S2_SD
PC4.GPIOParameters=GPIO_Label
PC4.GPIO_Label=SWITCH_0
PC4.Signal=GPIO_Input
PC5.GPIOParameters=GPIO_Label
PC5.GPIO_Label=SWITCH_1
PC5.Signal=GPIO_Input
PC6.Mode=Master_Clock_Activated
PC6.Signal=I2S2_MCK
RCC.HSE_VALUE=25000000
RCC.SYSCLKFreq_VALUE=16000000
board=custom

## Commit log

2024-06-09 Initial commit of the Basic DSP project
2024-06-10 Updates to basic DSP schematic
2024-06-11 Minor updates to Basic schematic
2024-06-13 Started layout
    Removed library from repo as it was messin with the links
2024-06-14 Basic placement on PCB
2024-06-19 Updated parts with LCSC order codes
2024-07-17 WIP - small layout progress on basic DSP
2024-07-18 more layout work on basic DSP
2024-08-25 Cleaned up the designators on Basic DSP layout
2024-08-29 More layout on Basic_DSP_V0_1 and a change of USB connector
2024-09-03 More layout work
2024-09-04 More layout updates
2024-09-05 Minor layout work
2024-09-06 Layout and removal of PDN ferrites
2024-09-08 All nets connected - DRC issues to be resolved
2024-09-09 No errors from DRC on layout
2024-09-12 Tidy layout ready for review
2024-10-14 Start of example FFT firmware
2024-10-20 Working FFT firmware
2024-11-25 Basic firmware to test hardware
2024-11-29 Basic firmware running. Audio in and out working well. All hardware except USB tested
2024-12-07 Working example of 2 peaking filters. Not perfect. Needs re-calculating (maybe) as it fails over 500Hz or so. Also not sure if it is cutting correctly...
2024-12-08 Working 3 band parametric EQ
